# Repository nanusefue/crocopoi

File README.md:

# Crocopoi

Crocopio is an OpenSource project that emulates a USB keyboard converting any conductive object as a switch.

https://www.oshwa.org/cert

**USB Keybord mapping **
http://www.freebsddiary.org/APC/usb_hid_usages.php

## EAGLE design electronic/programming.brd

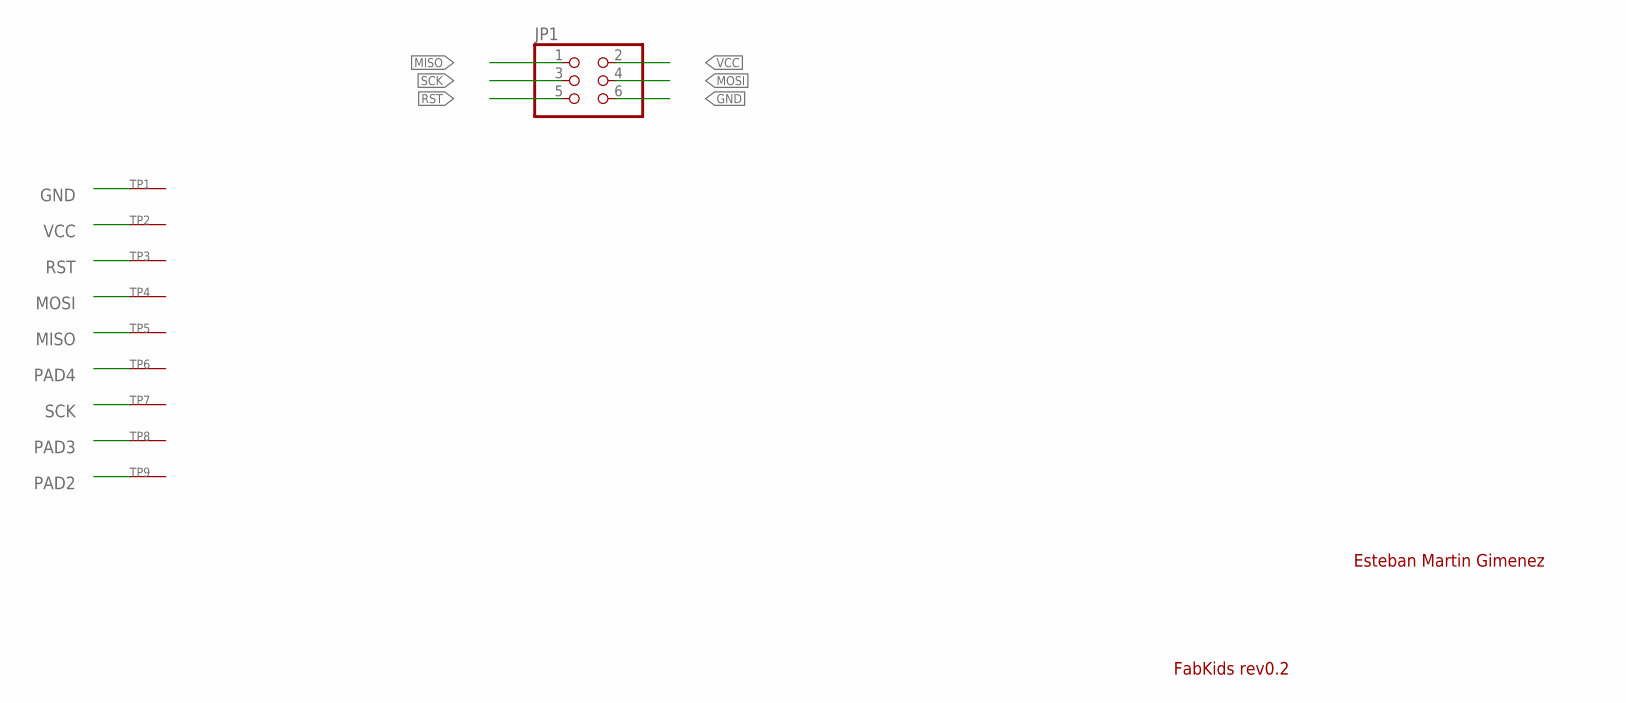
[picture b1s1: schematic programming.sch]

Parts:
JP1: PINHD-2X3-SMD; 2X03SMD
TP1, TP2, TP3, TP4, TP5, TP6, TP7, TP8, TP9: SEWTAP-2.0IN; SEWINGTAP_2.0

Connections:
GND: JP1.6, TP1.P$1
MISO: JP1.1, TP5.P$1
MOSI: JP1.4, TP4.P$1
PAD2: TP9.P$1
PAD3: TP8.P$1
PAD4: TP6.P$1
RST: JP1.5, TP3.P$1
SCK: JP1.3, TP7.P$1
VCC: JP1.2, TP2.P$1

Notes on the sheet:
Esteban Martin Gimenez
FabKids rev0.2

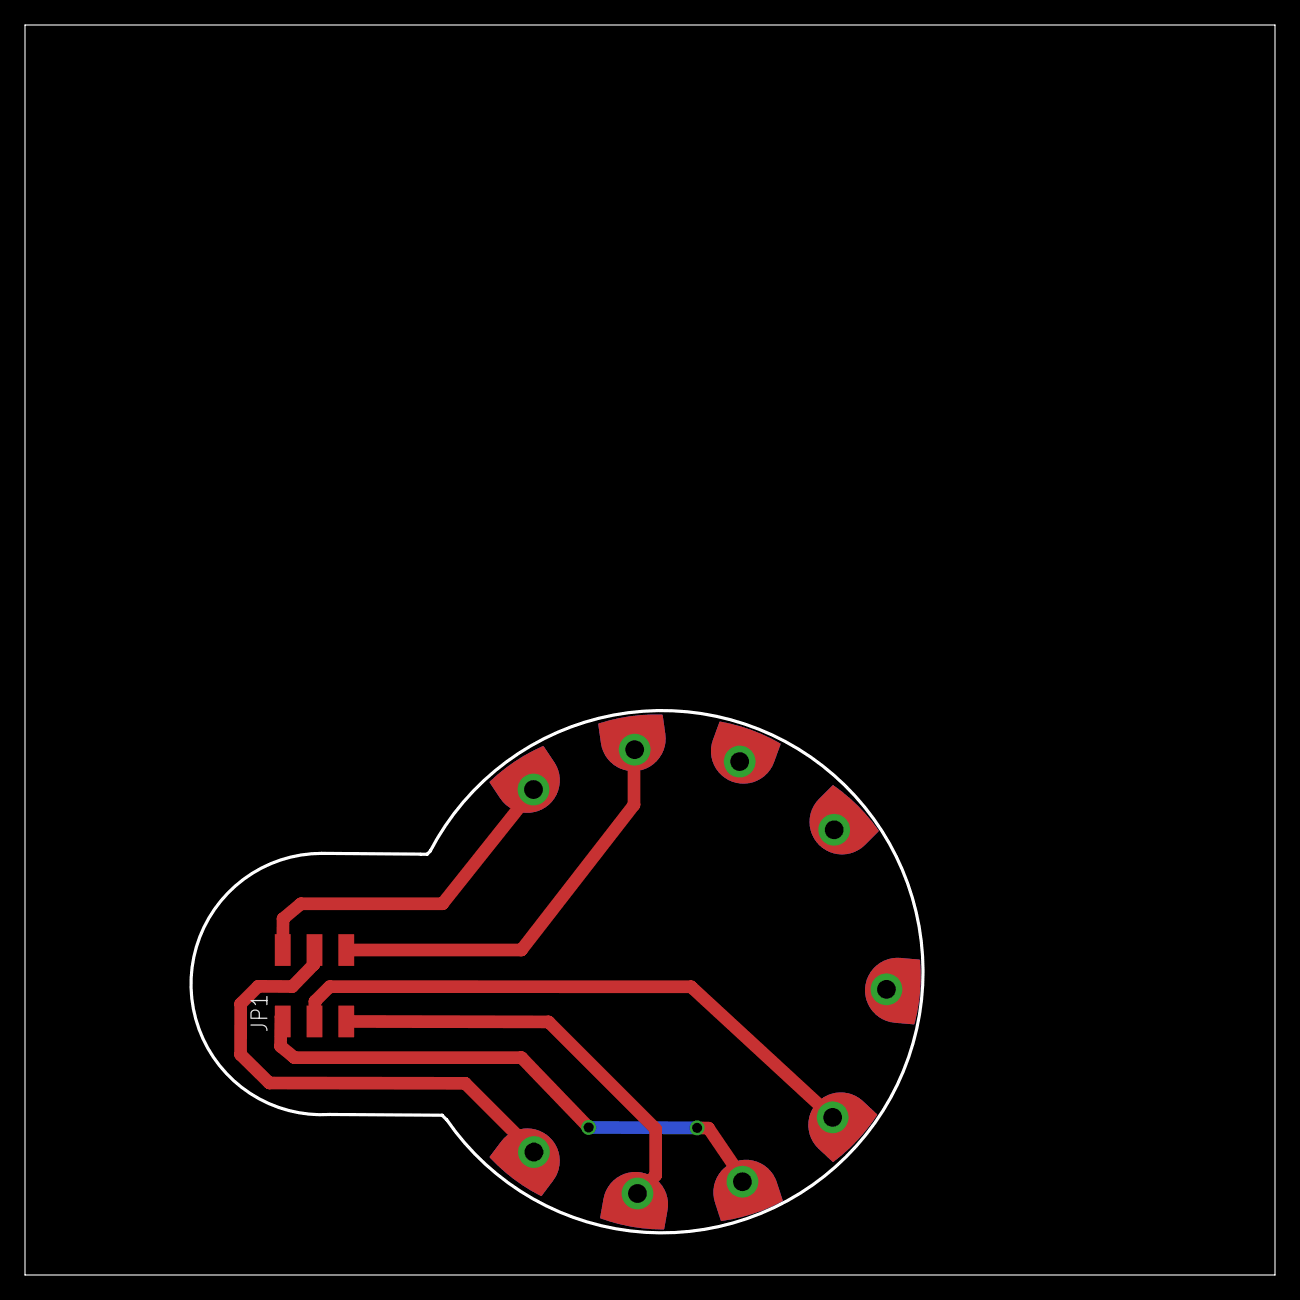
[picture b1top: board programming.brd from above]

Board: 2 copper layers, 100.0 x 100.0 mm, 10 parts (1 on the bottom side), 6 nets.

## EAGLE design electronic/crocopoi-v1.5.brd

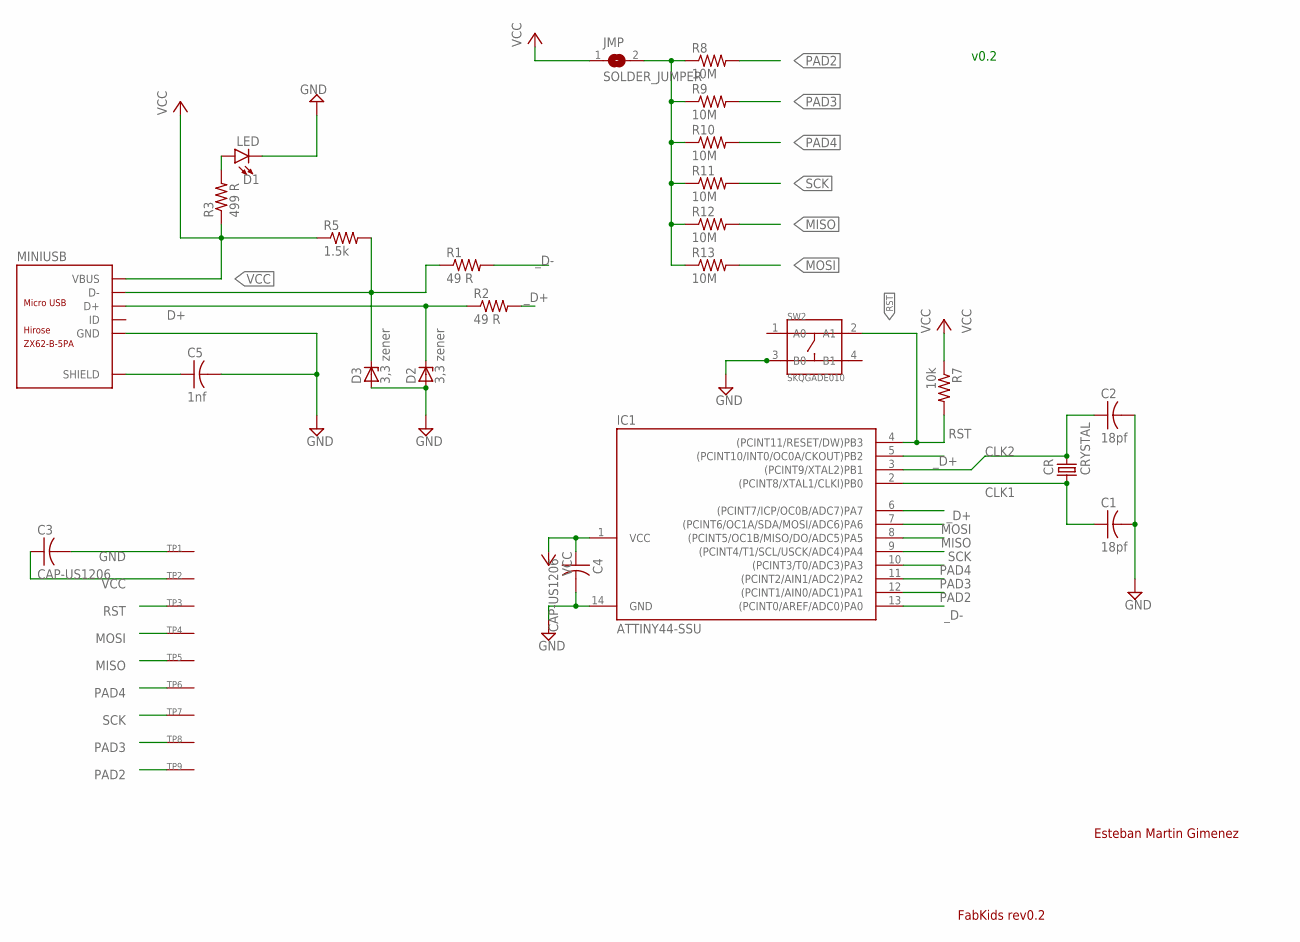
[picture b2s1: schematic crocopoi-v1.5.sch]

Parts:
C1, C2: 18pf; C1206FAB
C3, C4: CAP-US1206; C1206
C5: 1nf; C1206FAB
CR: CRYSTAL; 2-SMD-5X3MM
D1: LED; LED-1206
D2, D3: 3,3 zener; SOD123
IC1: ATTINY44-SSU; SOIC14
JMP: SOLDER_JUMPER; SJFAB
MINIUSB: ZX62-B-5PA; MICRO-USB5+6P-SMD-0.65-AB
R1, R2: 49 R; R1206FAB
R3: 499 R; R1206FAB
R5: 1.5k; R1206FAB
R7: 10k; R1206FAB
R8, R9, R10, R11, R12, R13: 10M; R1206FAB
SW2: SKQGADE010; SW4-SMD-5.2X5.2X1.5MM
TP1, TP2, TP3, TP4, TP5, TP6, TP7, TP8, TP9: SEWTAPBIG; BIGTAP

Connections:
CLK1: C1.1, CR.P$1 (1), IC1.2 ((PCINT8/XTAL1/CLKI)PB0)
CLK2: C2.1, CR.P$2 (2), IC1.3 ((PCINT9/XTAL2)PB1)
D+: D2.CATHODE, MINIUSB.3 (D+), R2.1
D-: D3.CATHODE, MINIUSB.2 (D-), R1.1, R5.2
GND: C1.2, C2.2, C3.2, C4.2, C5.2, D1.C, D2.ANODE, D3.ANODE, IC1.14 (GND), MINIUSB.5 (GND), SW2.3 (B0), TP1.P$1
MISO: IC1.8 ((PCINT5/OC1B/MISO/DO/ADC5)PA5), R12.2, TP5.P$1
MOSI: IC1.7 ((PCINT6/OC1A/SDA/MOSI/ADC6)PA6), R13.2, TP4.P$1
unnamed: JMP.2, R8.1, R9.1, R10.1, R11.1, R12.1, R13.1
unnamed: D1.A, R3.2
PAD2: IC1.12 ((PCINT1/AIN0/ADC1)PA1), R8.2, TP9.P$1
PAD3: IC1.11 ((PCINT2/AIN1/ADC2)PA2), R9.2, TP8.P$1
PAD4: IC1.10 ((PCINT3/T0/ADC3)PA3), R10.2, TP6.P$1
RST: IC1.4 ((PCINT11/RESET/DW)PB3), R7.2, SW2.2 (A1), TP3.P$1
SCK: IC1.9 ((PCINT4/T1/SCL/USCK/ADC4)PA4), R11.2, TP7.P$1
SHIELD: C5.1, MINIUSB.P1 (SHIELD), MINIUSB.P2 (SHIELD), MINIUSB.P3 (SHIELD), MINIUSB.P4 (SHIELD), MINIUSB.P5 (SHIELD), MINIUSB.P6 (SHIELD)
VCC: C3.1, C4.1, IC1.1 (VCC), JMP.1, MINIUSB.1 (VBUS), R3.1, R5.1, R7.1, TP2.P$1
_D+: IC1.5 ((PCINT10/INT0/OC0A/CKOUT)PB2), IC1.6 ((PCINT7/ICP/OC0B/ADC7)PA7), R2.2
_D-: IC1.13 ((PCINT0/AREF/ADC0)PA0), R1.2

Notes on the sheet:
Esteban Martin Gimenez
FabKids rev0.2
v0.2

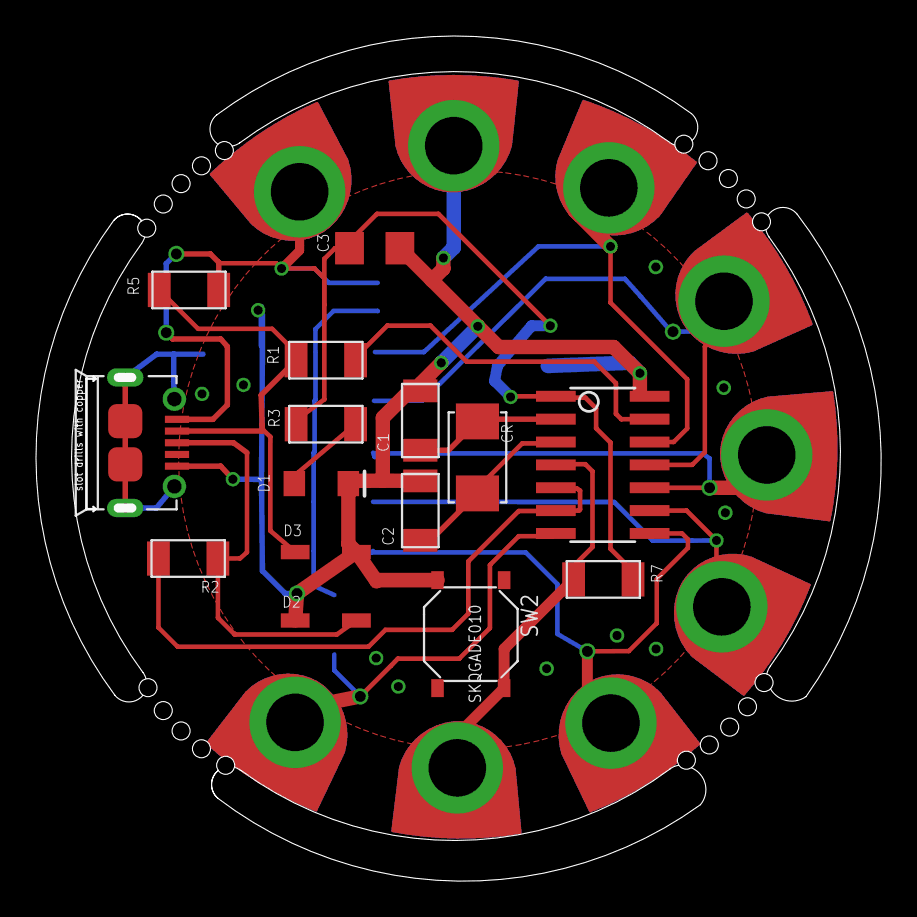
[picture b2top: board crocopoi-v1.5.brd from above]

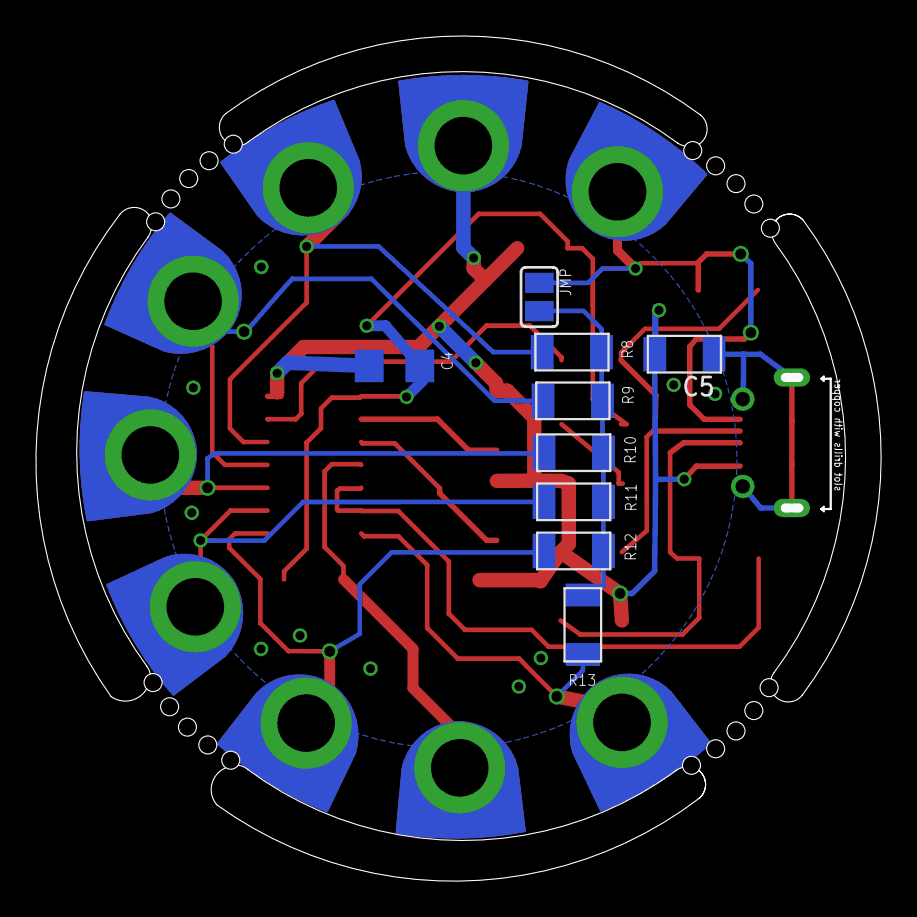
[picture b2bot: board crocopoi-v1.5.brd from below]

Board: 2 copper layers, 47.0 x 47.0 mm, 33 parts (10 on the bottom side), 18 nets.

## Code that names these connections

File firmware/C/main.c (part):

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bool inputChanged;
/* ------------------------------------------------------------------------- */
uint8_t pinNumbers[NUM_INPUTS] = {
  _BV(PA1), _BV(PA2), _BV(PA3), _BV(PA4), _BV(PA5), _BV(PA6)
};

typedef struct {
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
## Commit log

2018-12-02 add C and arduino source code
2018-12-02 add pdf
2018-12-03 add hardware licence
2018-12-03 add licence hardware

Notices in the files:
firmware/C/main.c:
Copyright 2018 Esteban Martin Gimenez
This program is free software: you can redistribute it and/or modify
it under the terms of the GNU General Public License as published by
the Free Software Foundation, either version 3 of the License, or
(at your option) any later version.
parts and their libraries:
SparkFun-LED: Licensing: Creative Commons ShareAlike 4.0 International - https://creativecommons.org/licenses/by-sa/4.0
